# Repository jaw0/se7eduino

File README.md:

small atmel SAM S70 (300MHz cortex-M7) based dev board.
similar to the arduino due, except super-mega-turbocharged.

* 300 MHz ARM cortex-M7
* 2MB flash
* 384k RAM
* 480 Mbps high-speed USB
* micro sd card
* battery charger
* 64 x 34 mm

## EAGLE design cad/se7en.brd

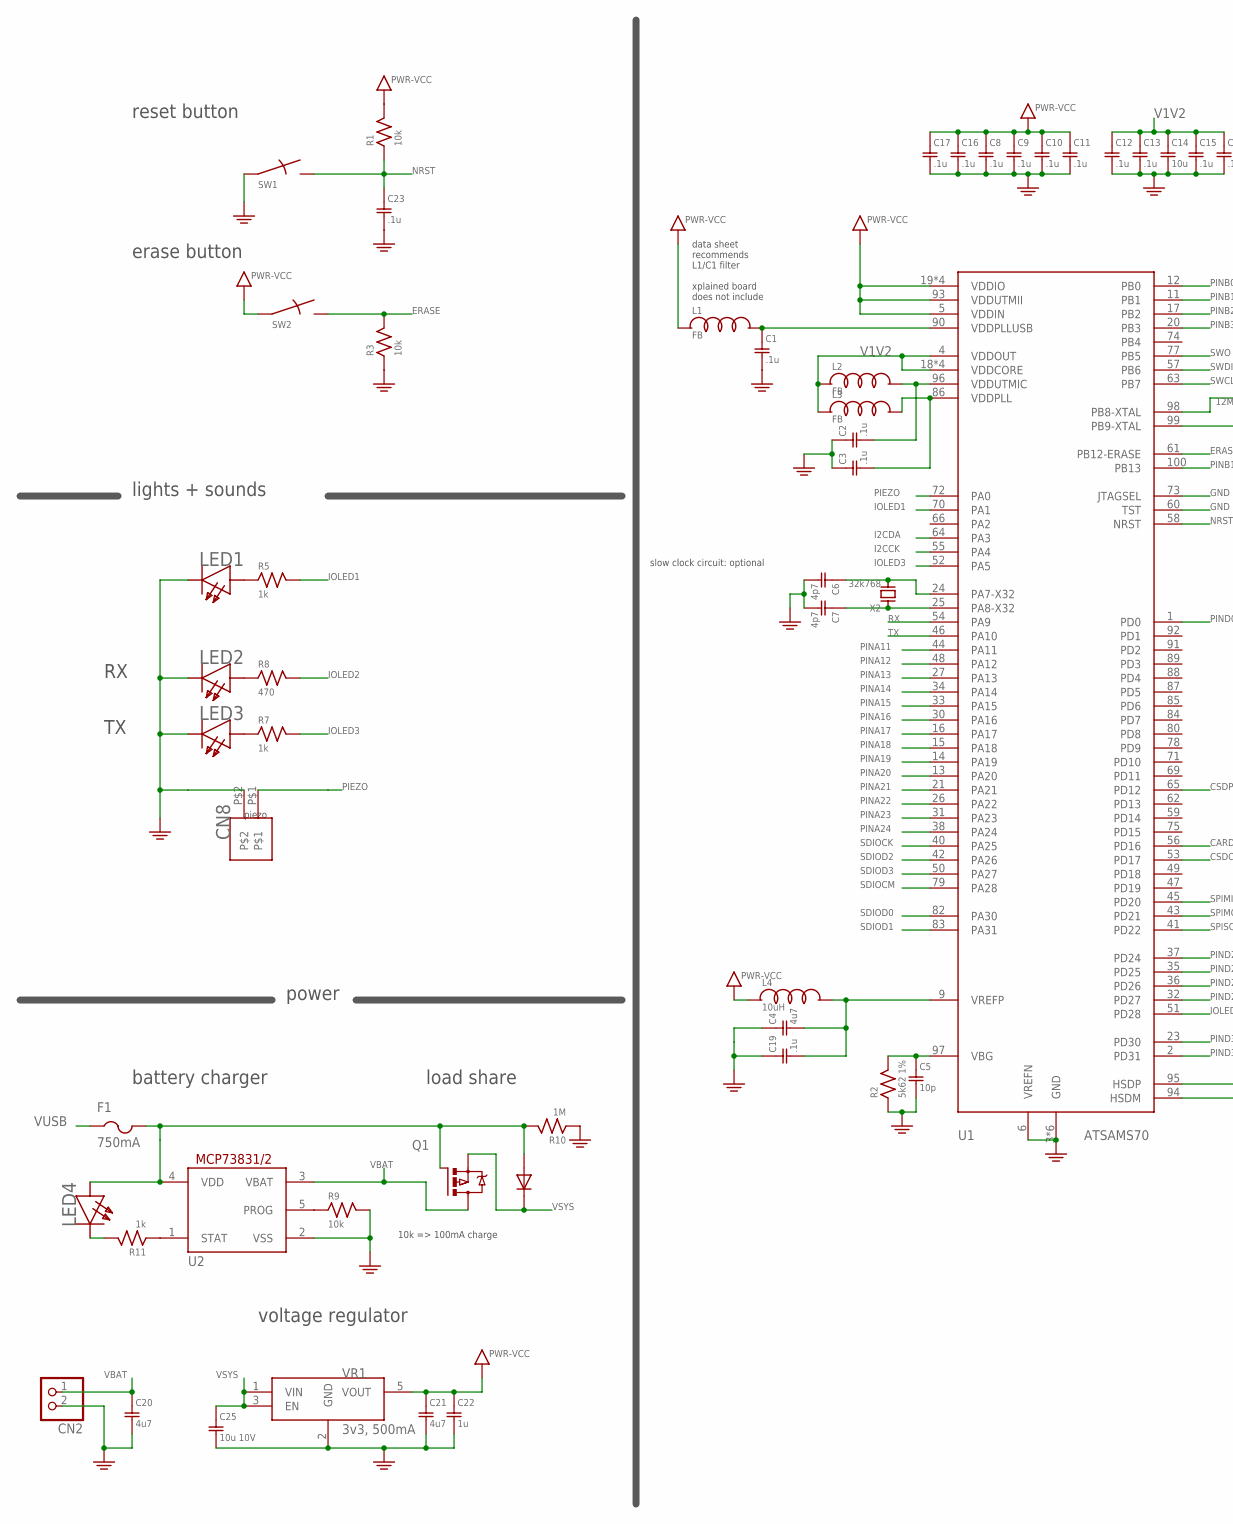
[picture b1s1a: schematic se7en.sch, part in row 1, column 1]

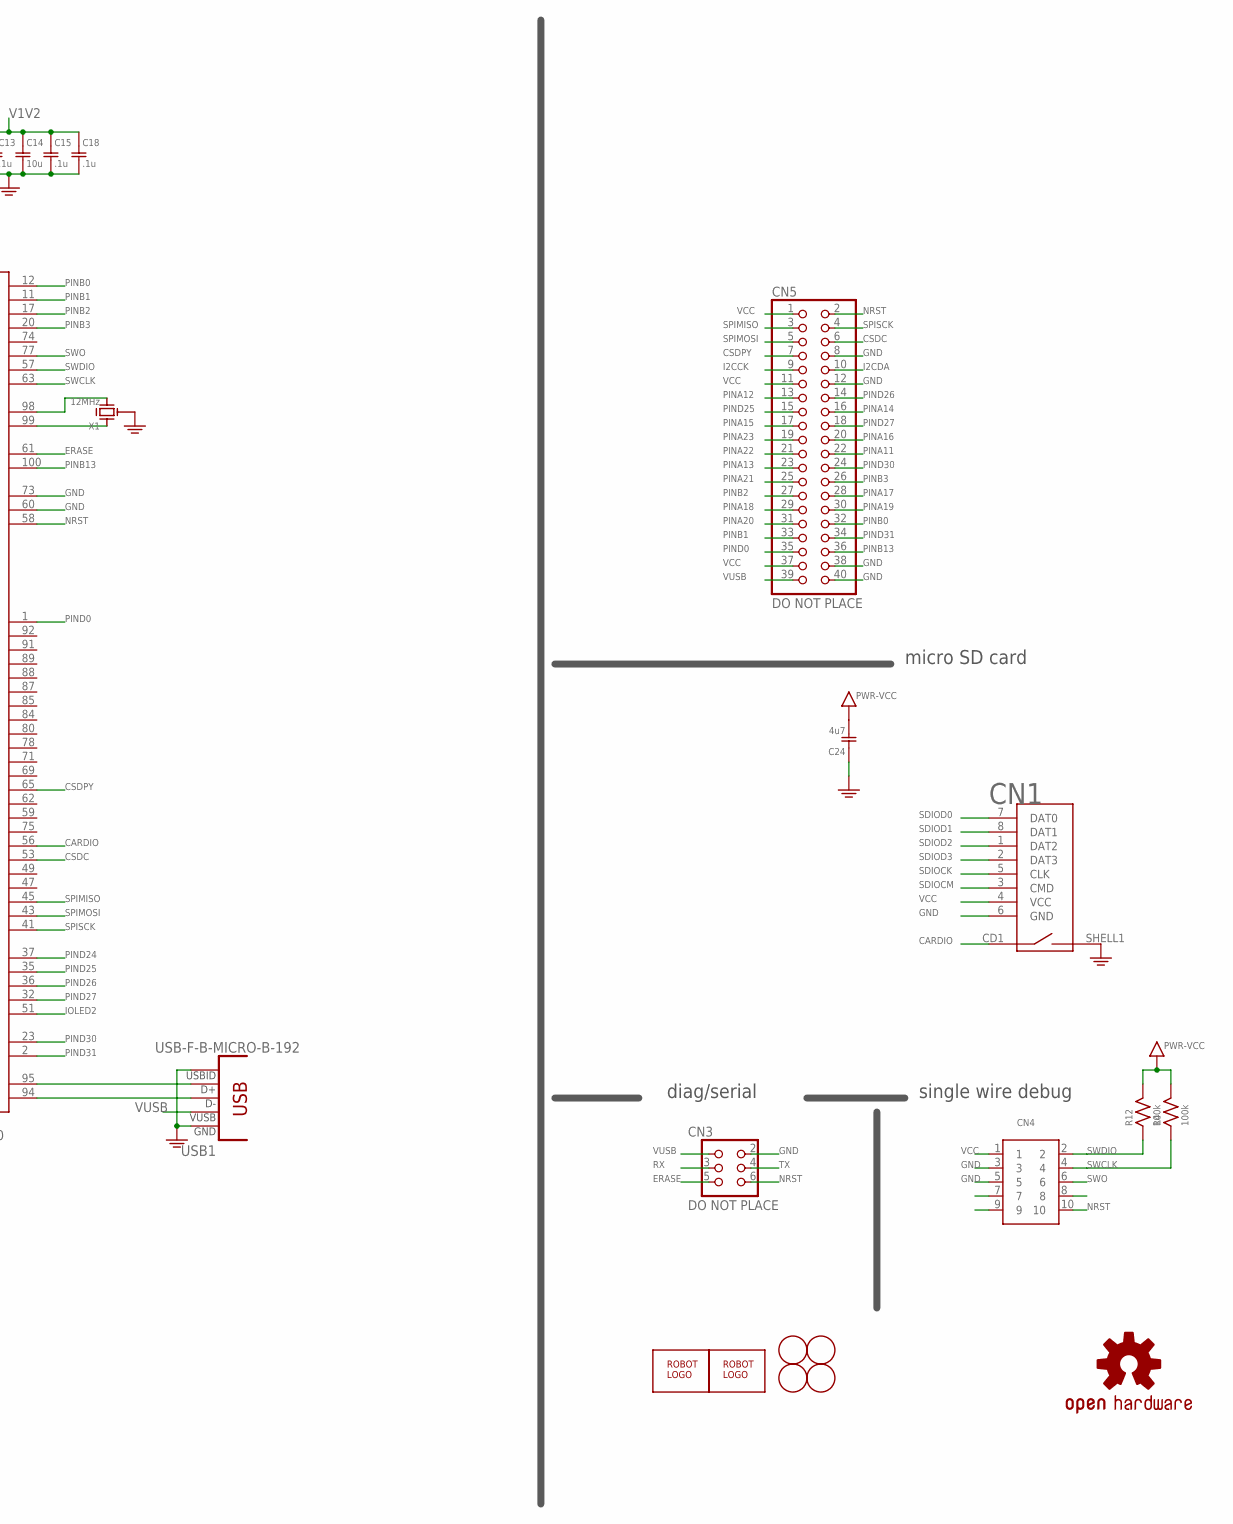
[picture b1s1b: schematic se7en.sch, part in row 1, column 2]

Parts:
C1, C2, C3, C8, C9, C10, C11, C12, C13, C15, C16, C17, C18, C19, C23: .1u; SMD0402
C4, C20, C21, C24: 4u7; SMD0603
C5: 10p; SMD0402
C6, C7: 4p7; SMD0402
C14: 10u; SMD0603
C22: 1u; SMD0603
C25: 10u 10V; SMD0603
CN1: MICROSD-EJECT; MICROSD/EJECTOR
CN2: JST_2PIN-SMT-RA; JST-PH-2-SMT-RA
CN3: DO NOT PLACE; HEADER-3X2-POGO
CN4: DO NOT PLACE; M127-5X2-F
CN5: DO NOT PLACE; 2X20
CN8: DO NOT PLACE; HEADER-1X2-THM-TIGHT
F1: 750mA; SMD1206
L1, L2, L3: FB; SMD0402
L4: 10uH; SMD0603
LED1: white; SMD0603D
LED2: green; SMD0603D
LED3: orange; SMD0603D
LED4: RED; SMD0603D
LOGO$1: OSHW-LOGOM; OSHW-LOGO-M
Q1: FDC6392S; SOT-23-6
R1, R3, R9: 10k; SMD0402
R2: 5k62 1%; SMD0402
R4, R12: 100k; SMD0402
R5, R7, R11: 1k; SMD0402
R8: 470; SMD0402
R10: 1M; SMD0402
SW1, SW2: SWITCHKMR211; KMR211
U1: ATSAMS70; TQFP-100-14X14MM
U2: MCP73831; SOT-23-5
U$1, U$3: ROBOTMAN-LOGO2
U$2, U$4, U$5, U$6: FIDUCIAL; FIDUCIAL_1MM
USB1: USB-F-B-MICRO-B-192; USB-MICRO-B-192
VR1: 3v3, 500mA; SOT-23-5
X1: 12MHz; RESONATOR-CSTCE
X2: 32k768; XTAL-32X15

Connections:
CARDIO: CN1.CD1 (SW1), U1.56 (PD16)
CSDC: CN5.6, U1.53 (PD17)
CSDPY: CN5.7, U1.65 (PD12)
ERASE: CN3.5, R3.2, SW2.2, SW2.4, U1.61 (PB12-ERASE)
GND: C1.2, C2.1, C3.1, C4.1, C5.2, C6.2, C7.2, C8.2, C9.2, C10.2, C11.2, C12.2, C13.2, C14.2, C15.2, C16.2, C17.2, C18.2, C19.1, C20.2, C21.2, C22.2, C23.2, C24.1, C25.2, CN1.6 (GND), CN1.SHELL1 (SW2), CN2.2 (1), CN3.2, CN4.3, CN4.5, CN5.8, CN5.12, CN5.38, CN5.40, CN8.P$2, LED1.C, LED2.C, LED3.C, R2.1, R3.1, R9.2, R10.1, SW1.1, SW1.3, U1.3 (GND), U1.6 (VREFN), U1.7 (GND), U1.8 (GND), U1.10 (GND), U1.29 (GND), U1.60 (TST), U1.67 (GND), U1.73 (JTAGSEL), U2.2 (VSS), USB1.P4 (USBID), USB1.P5 (GND), VR1.2 (GND), X1.2 (G)
I2CCK: CN5.9, U1.55 (PA4)
I2CDA: CN5.10, U1.64 (PA3)
IOLED1: R5.2, U1.70 (PA1)
IOLED2: R8.2, U1.51 (PD28)
IOLED3: R7.2, U1.52 (PA5)
unnamed: C2.2, L2.2, U1.96 (VDDUTMIC)
unnamed: C1.1, L1.2, U1.90 (VDDPLLUSB)
unnamed: C3.2, L3.2, U1.86 (VDDPLL)
unnamed: LED2.A, R8.1
unnamed: LED3.A, R7.1
unnamed: U1.98 (PB8-XTAL), X1.3 (X2)
unnamed: C5.1, R2.2, U1.97 (VBG)
unnamed: U1.99 (PB9-XTAL), X1.1 (X1)
unnamed: C7.1, U1.25 (PA8-X32), X2.P$1
unnamed: R11.1, U2.1 (STAT)
unnamed: C6.1, U1.24 (PA7-X32), X2.P$2
unnamed: LED4.C, R11.2
unnamed: LED1.A, R5.1
unnamed: R9.1, U2.5 (PROG)
NRST: C23.1, CN3.6, CN4.10, CN5.2, R1.1, SW1.2, SW1.4, U1.58 (NRST)
PIEZO: CN8.P$1, U1.72 (PA0)
PINA11: CN5.22, U1.44 (PA11)
PINA12: CN5.13, U1.48 (PA12)
PINA13: CN5.23, U1.27 (PA13)
PINA14: CN5.16, U1.34 (PA14)
PINA15: CN5.17, U1.33 (PA15)
PINA16: CN5.20, U1.30 (PA16)
PINA17: CN5.28, U1.16 (PA17)
PINA18: CN5.29, U1.15 (PA18)
PINA19: CN5.30, U1.14 (PA19)
PINA20: CN5.31, U1.13 (PA20)
PINA21: CN5.25, U1.21 (PA21)
PINA22: CN5.21, U1.26 (PA22)
PINA23: CN5.19, U1.31 (PA23)
PINA24: U1.38 (PA24)
PINB0: CN5.32, U1.12 (PB0)
PINB1: CN5.33, U1.11 (PB1)
PINB2: CN5.27, U1.17 (PB2)
PINB3: CN5.26, U1.20 (PB3)
PINB13: CN5.36, U1.100 (PB13)
PIND0: CN5.35, U1.1 (PD0)
PIND24: U1.37 (PD24)
PIND25: CN5.15, U1.35 (PD25)
PIND26: CN5.14, U1.36 (PD26)
PIND27: CN5.18, U1.32 (PD27)
PIND30: CN5.24, U1.23 (PD30)
PIND31: CN5.34, U1.2 (PD31)
RX: CN3.3, U1.54 (PA9)
SDIOCK: CN1.5 (CLK), U1.40 (PA25)
SDIOCM: CN1.3 (CMD), U1.79 (PA28)
SDIOD0: CN1.7 (DAT0), U1.82 (PA30)
SDIOD1: CN1.8 (DAT1), U1.83 (PA31)
SDIOD2: CN1.1 (DAT2), U1.42 (PA26)
SDIOD3: CN1.2 (DAT3), U1.50 (PA27)
SPIMISO: CN5.3, U1.45 (PD20)
SPIMOSI: CN5.5, U1.43 (PD21)
SPISCK: CN5.4, U1.41 (PD22)
SWCLK: CN4.4, R4.1, U1.63 (PB7)
SWDIO: CN4.2, R12.1, U1.57 (PB6)
SWO: CN4.6, U1.77 (PB5)
TX: CN3.4, U1.46 (PA10)
USBDM: U1.94 (HSDM), USB1.P2 (D-)
USBDP: U1.95 (HSDP), USB1.P3 (D+)
V1V2: C12.1, C13.1, C14.1, C15.1, C18.1, L2.1, L3.1, U1.4 (VDDOUT), U1.18 (VDDCORE), U1.22 (VDDCORE), U1.39 (VDDCORE), U1.76 (VDDCORE)
VBAT: C20.1, CN2.1 (2), Q1.4 (D), U2.3 (VBAT)
VCC: C8.1, C9.1, C10.1, C11.1, C16.1, C17.1, C21.1, C22.1, C24.2, CN1.4 (VCC), CN4.1, CN5.1, CN5.11, CN5.37, L1.1, L4.1, R1.2, R4.2, R12.2, SW2.1, SW2.3, U1.5 (VDDIN), U1.19 (VDDIO), U1.28 (VDDIO), U1.68 (VDDIO), U1.81 (VDDIO), U1.93 (VDDUTMII), VR1.5 (VOUT)
VCCA: C4.2, C19.2, L4.2, U1.9 (VREFP)
VIN: F1.2, LED4.A, Q1.1 (A), Q1.3 (G), R10.2, U2.4 (VDD)
VSYS: C25.1, Q1.2 (S), Q1.6 (C), VR1.1 (VIN), VR1.3 (EN)
VUSB: CN3.1, CN5.39, F1.1, USB1.P1 (VUSB)

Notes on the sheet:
piezo
battery charger
load share
voltage regulator
diag/serial
single wire debug
micro SD card
reset button
erase button
lights + sounds
power
slow clock circuit: optional
data sheet recommends L1/C1 filter xplained board does not include
10k => 100mA charge

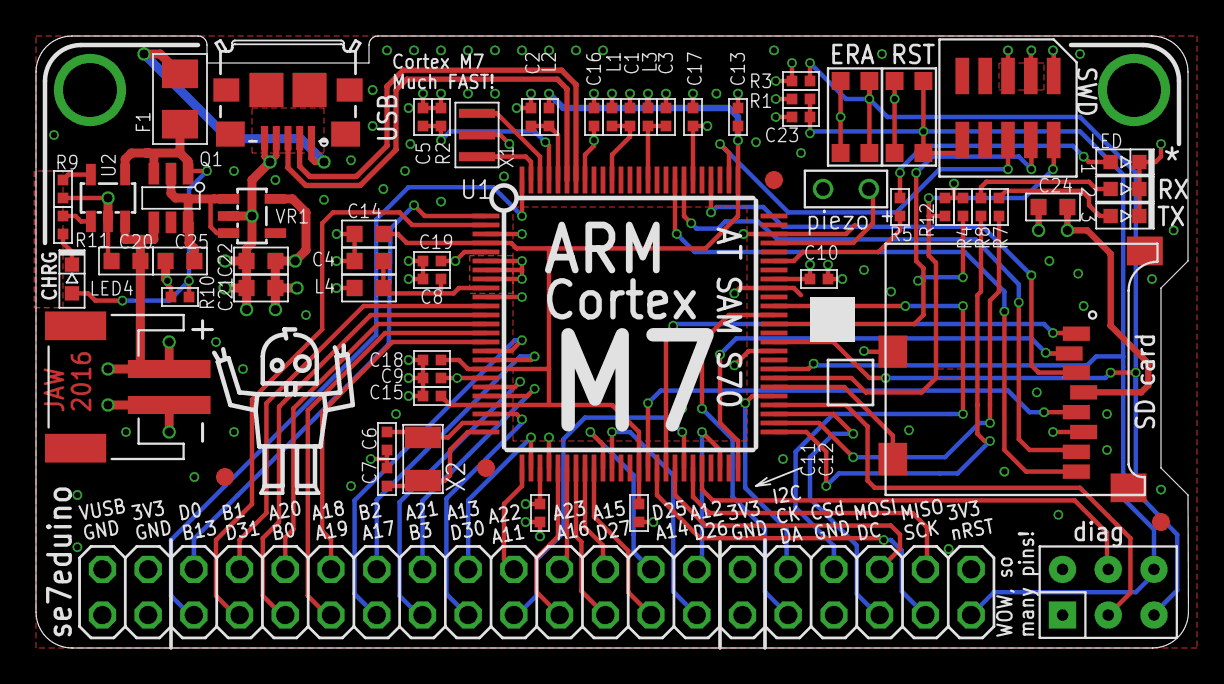
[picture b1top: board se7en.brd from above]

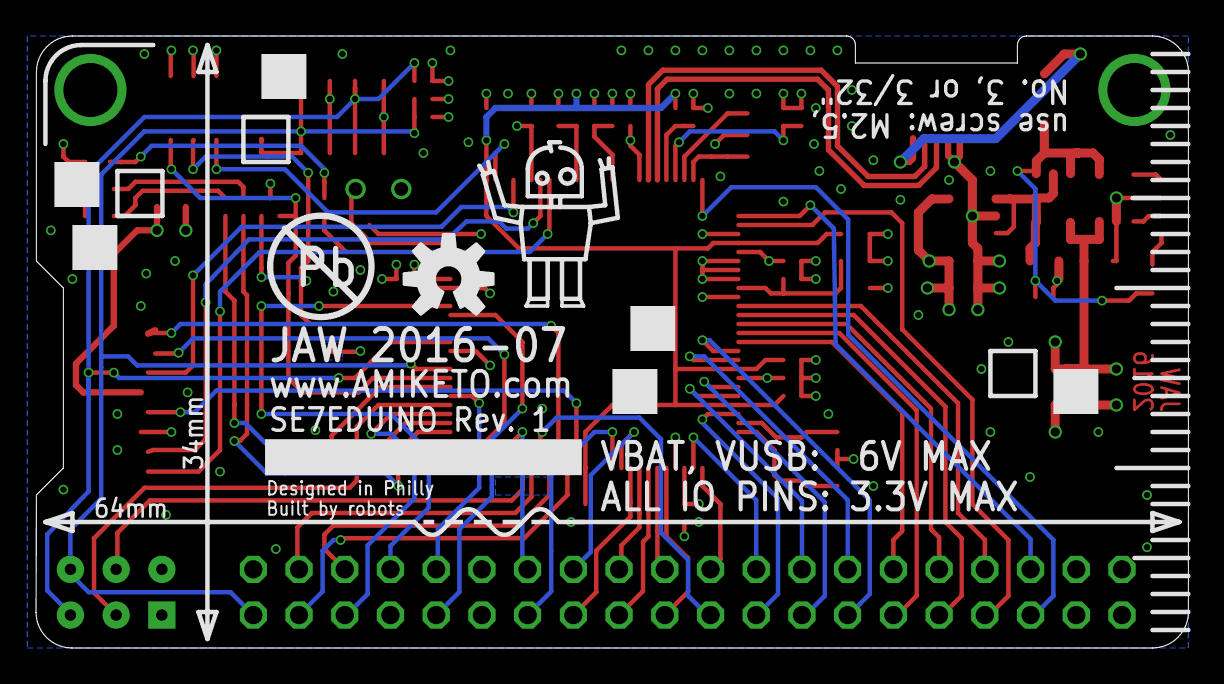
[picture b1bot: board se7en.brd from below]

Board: 4 copper layers, 64.0 x 34.0 mm, 67 parts (2 on the bottom side), 73 nets.

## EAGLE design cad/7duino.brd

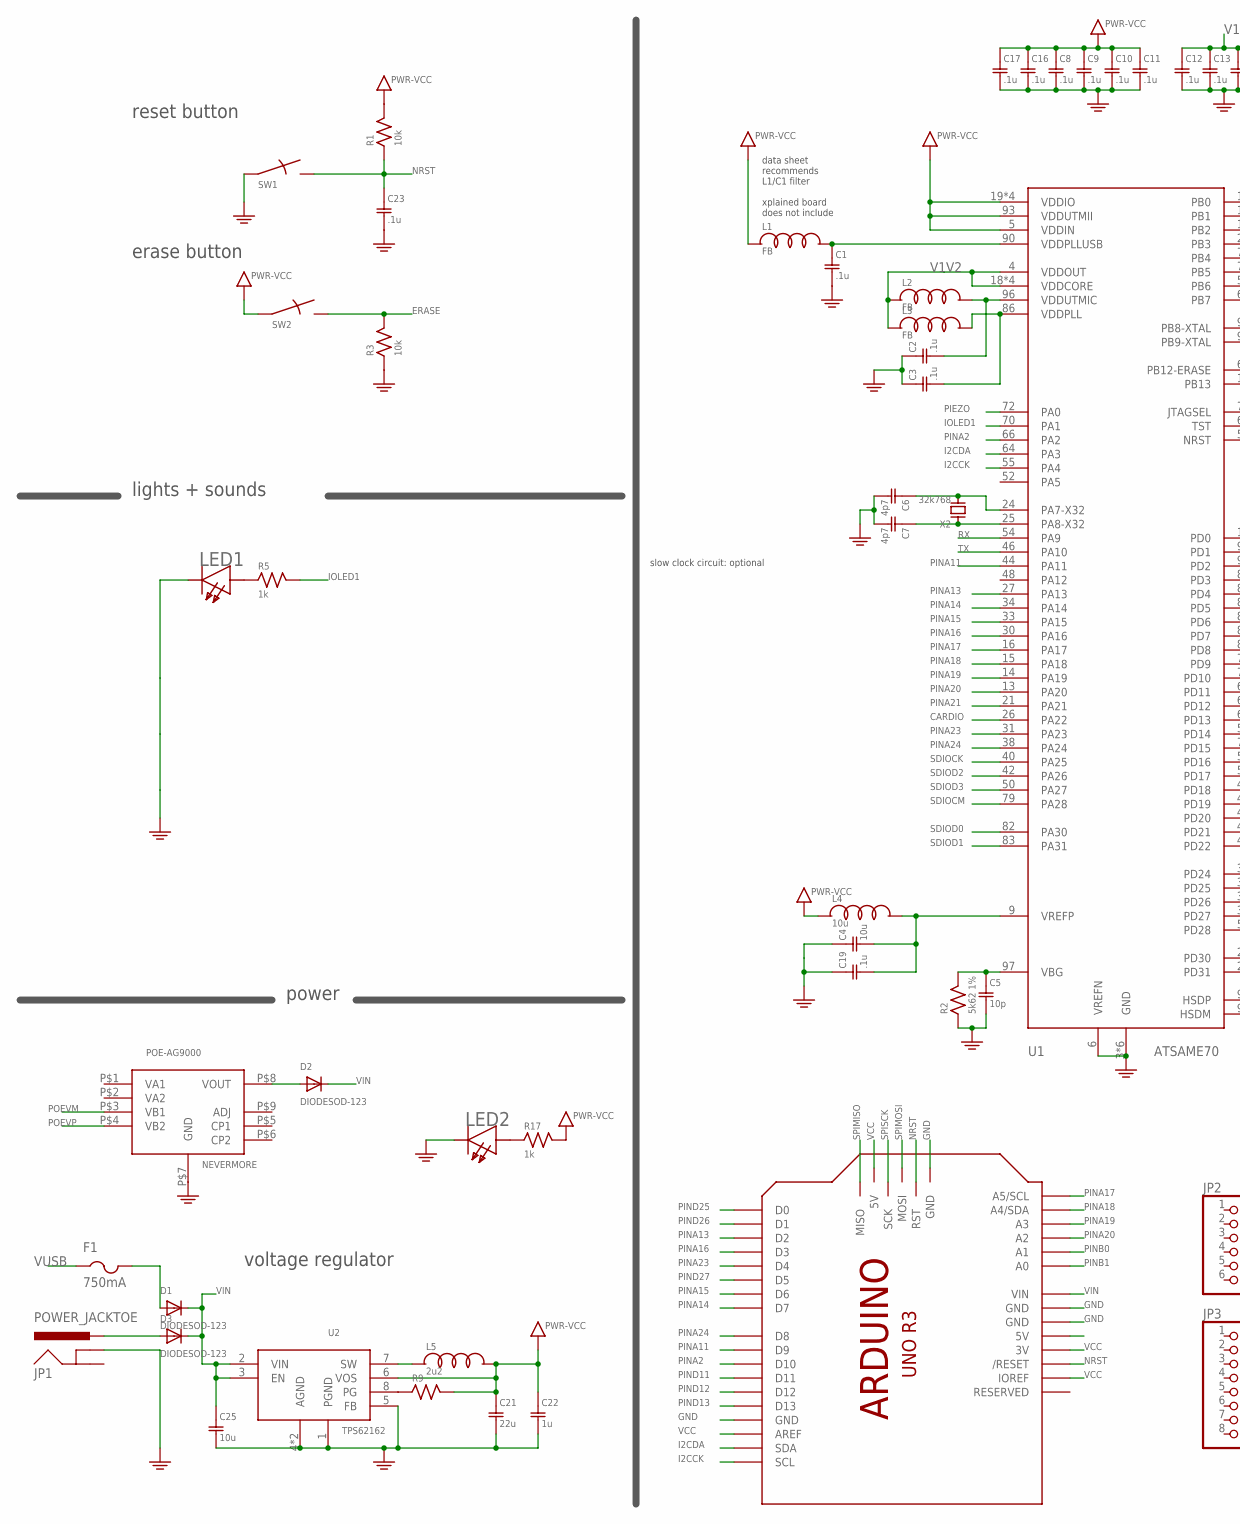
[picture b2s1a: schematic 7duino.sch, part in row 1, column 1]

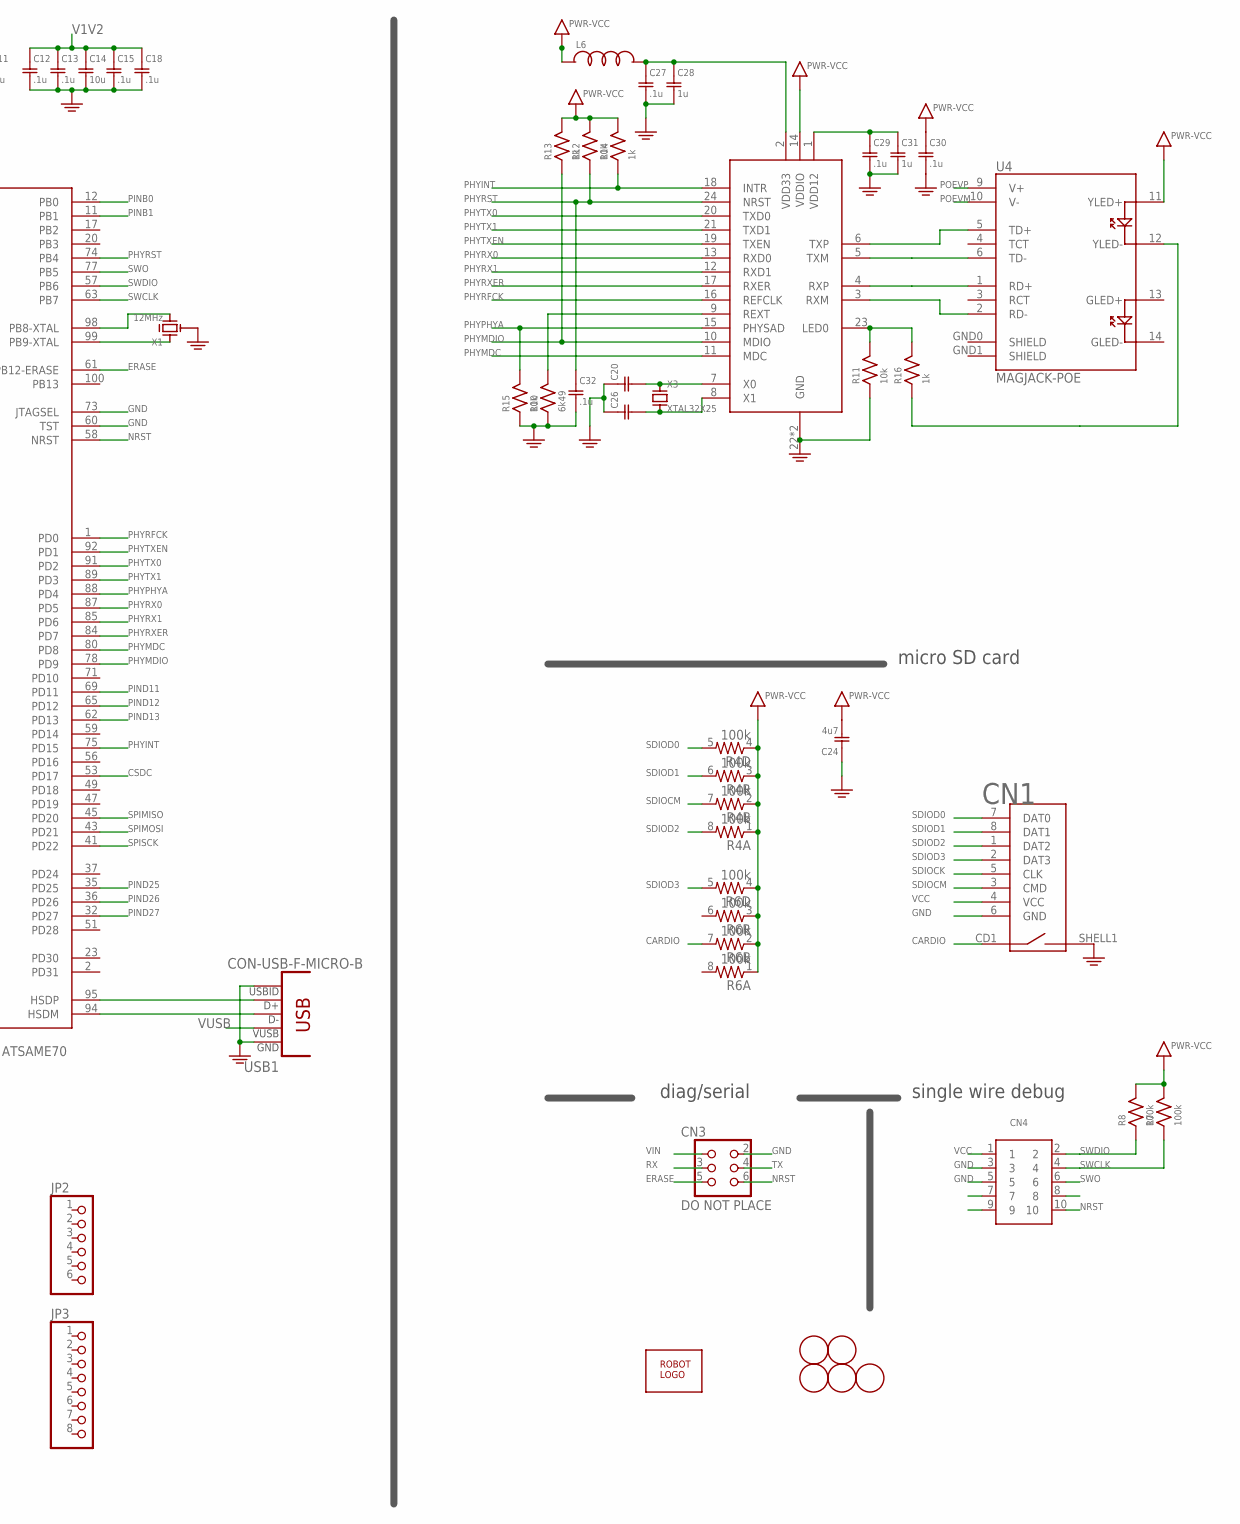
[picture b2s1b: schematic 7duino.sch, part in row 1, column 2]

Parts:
C1, C2, C3, C8, C9, C10, C11, C12, C13, C15, C16, C17, C18, C19, C23, C27, C29, C30, C32: .1u; SMD0402
C4, C14, C25: 10u; SMD0603
C5: 10p; SMD0402
C6, C7: 4p7; SMD0402
C20, C26: C-0402; SMD0402
C21: 22u; SMD0805
C22, C28, C31: 1u; SMD0402
C24: 4u7; SMD0603
CN1: MICROSD-EJECT; MICROSD/EJECTOR
CN3: DO NOT PLACE; HEADER-3X2-POGO
CN4: DO NOT PLACE; M127-5X2-F
D1, D2, D3: DIODESOD-123; SOD-123
F1: 750mA; SMD1206
JP1: POWER_JACKTOE; POWER_JACK_SMD_OVERPASTE_TOE
JP2: PINHD-1X6CLEAN; 1X06-CLEAN
JP3: PINHD-1X8CLEANBIG; 1X08-CLEANBIG
L1, L2, L3: FB; SMD0402
L4: 10u; SMD0402
L5: 2u2; SMD1210
L6: L-0402; SMD0402
LED1, LED2: white; SMD0603D
M1: ARDUINO_R3_ICSP_NODIM; ARDUINOR3_ICSP_NODIM
NEVERMORE: POE-AG9000
R1, R3, R11, R12, R15: 10k; SMD0402
R2: 5k62 1%; SMD0402
R4, R6: 100k; SMD-0603-ARV
R5, R13, R14, R16, R17: 1k; SMD0402
R7, R8: 100k; SMD0402
R9: R-0402; SMD0402
R10: 6k49; SMD0402
SW1, SW2: SWITCHKMR211; KMR211
U1: ATSAME70; TQFP-100-14X14MM
U2: TPS62162; WSON8
U3: KSZ8081RNA; LGA24EP
U4: MAGJACK-POE
U$1: ROBOTMAN-LOGO2
U$2, U$3, U$4, U$5, U$6: FIDUCIAL; FIDUCIAL_1MM
USB1: CON-USB-F-MICRO-B; CONN_USB_MICRO-B
X1: 12MHz; RESONATOR-CSTCE
X2: 32k768; XTAL-32X15
X3: XTAL32X25; XTAL-32X25

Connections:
CARDIO: CN1.CD1 (SW1), R6.7 (2), U1.26 (PA22)
CSDC: U1.53 (PD17)
ERASE: CN3.5, R3.2, SW2.2, SW2.4, U1.61 (PB12-ERASE)
GND: C1.2, C2.1, C3.1, C4.1, C5.2, C6.2, C7.2, C8.2, C9.2, C10.2, C11.2, C12.2, C13.2, C14.2, C15.2, C16.2, C17.2, C18.2, C19.1, C20.1, C21.2, C22.2, C23.2, C24.1, C25.2, C26.1, C27.2, C28.2, C29.2, C30.2, C31.2, C32.2, CN1.6 (GND), CN1.SHELL1 (SW2), CN3.2, CN4.3, CN4.5, JP1.GND (GNDBREAK), LED1.C, LED2.C, M1.GND, M1.GND@1 (GND), M1.GND@2 (GND), M1.GND@3 (GND), NEVERMORE.P$7 (GND), R2.1, R3.1, R10.1, R11.1, R15.1, SW1.1, SW1.3, U1.3 (GND), U1.6 (VREFN), U1.7 (GND), U1.8 (GND), U1.10 (GND), U1.29 (GND), U1.60 (TST), U1.67 (GND), U1.73 (JTAGSEL), U2.1 (PGND), U2.4 (AGND), U2.5 (FB), U2.P$9 (AGND), U3.22 (GND), U3.P$1 (GND), USB1.P4 (USBID), USB1.P5 (GND), X1.2 (G)
I2CCK: M1.SCL, U1.55 (PA4)
I2CDA: M1.SDA, U1.64 (PA3)
IOLED1: R5.2, U1.70 (PA1)
unnamed: C2.2, L2.2, U1.96 (VDDUTMIC)
unnamed: C1.1, L1.2, U1.90 (VDDPLLUSB)
unnamed: C3.2, L3.2, U1.86 (VDDPLL)
unnamed: LED2.A, R17.1
unnamed: D2.A, NEVERMORE.P$8 (VOUT)
unnamed: U1.98 (PB8-XTAL), X1.3 (X2)
unnamed: C5.1, R2.2, U1.97 (VBG)
unnamed: U1.99 (PB9-XTAL), X1.1 (X1)
unnamed: C7.1, U1.25 (PA8-X32), X2.P$1
unnamed: L5.1, U2.7 (SW)
unnamed: C6.1, U1.24 (PA7-X32), X2.P$2
unnamed: U3.6 (TXP), U4.5 (TD+)
unnamed: D3.A, JP1.VIN0 (PWR)
unnamed: LED1.A, R5.1
unnamed: U3.5 (TXM), U4.6 (TD-)
unnamed: R9.1, U2.8 (PG)
unnamed: U3.4 (RXP), U4.1 (RD+)
unnamed: U3.3 (RXM), U4.2 (RD-)
unnamed: C20.2, U3.7 (X0), X3.1
unnamed: C26.2, U3.8 (X1), X3.3
unnamed: C29.1, C31.1, U3.1 (VDD12)
unnamed: C27.1, C28.1, L6.2, U3.2 (VDD33)
unnamed: R10.2, U3.9 (REXT)
unnamed: R11.2, R16.2, U3.23 (LED0)
unnamed: D1.A, F1.2
unnamed: R16.1, U4.12 (YLED-)
NRST: C23.1, CN3.6, CN4.10, M1.RESET (/RESET), M1.RESET_ICSP (RST), R1.1, SW1.2, SW1.4, U1.58 (NRST)
PHYINT: R14.1, U1.75 (PD15), U3.18 (INTR)
PHYMDC: U1.80 (PD8), U3.11 (MDC)
PHYMDIO: R13.1, U1.78 (PD9), U3.10 (MDIO)
PHYPHYA: R15.2, U1.88 (PD4), U3.15 (PHYSAD)
PHYRFCK: U1.1 (PD0), U3.16 (REFCLK)
PHYRST: C32.1, R12.1, U1.74 (PB4), U3.24 (NRST)
PHYRX0: U1.87 (PD5), U3.13 (RXD0)
PHYRX1: U1.85 (PD6), U3.12 (RXD1)
PHYRXER: U1.84 (PD7), U3.17 (RXER)
PHYTX0: U1.91 (PD2), U3.20 (TXD0)
PHYTX1: U1.89 (PD3), U3.21 (TXD1)
PHYTXEN: U1.92 (PD1), U3.19 (TXEN)
PIEZO: U1.72 (PA0)
PINA2: M1.D10, U1.66 (PA2)
PINA11: M1.D9, U1.44 (PA11)
PINA13: M1.D2, U1.27 (PA13)
PINA14: M1.D7, U1.34 (PA14)
PINA15: M1.D6, U1.33 (PA15)
PINA16: M1.D3, U1.30 (PA16)
PINA17: M1.A5 (A5/SCL), U1.16 (PA17)
PINA18: M1.A4 (A4/SDA), U1.15 (PA18)
PINA19: M1.A3, U1.14 (PA19)
PINA20: M1.A2, U1.13 (PA20)
PINA21: U1.21 (PA21)
PINA23: M1.D4, U1.31 (PA23)
PINA24: M1.D8, U1.38 (PA24)
PINB0: M1.A1, U1.12 (PB0)
PINB1: M1.A0, U1.11 (PB1)
PIND11: M1.D11, U1.69 (PD11)
PIND12: M1.D12, U1.65 (PD12)
PIND13: M1.D13, U1.62 (PD13)
PIND25: M1.D0, U1.35 (PD25)
PIND26: M1.D1, U1.36 (PD26)
PIND27: M1.D5, U1.32 (PD27)
POEVM: NEVERMORE.P$3 (VB1), U4.10 (V-)
POEVP: NEVERMORE.P$4 (VB2), U4.9 (V+)
RX: CN3.3, U1.54 (PA9)
SDIOCK: CN1.5 (CLK), U1.40 (PA25)
SDIOCM: CN1.3 (CMD), R4.7 (2), U1.79 (PA28)
SDIOD0: CN1.7 (DAT0), R4.5 (2), U1.82 (PA30)
SDIOD1: CN1.8 (DAT1), R4.6 (2), U1.83 (PA31)
SDIOD2: CN1.1 (DAT2), R4.8 (2), U1.42 (PA26)
SDIOD3: CN1.2 (DAT3), R6.5 (2), U1.50 (PA27)
SPIMISO: M1.MISO, U1.45 (PD20)
SPIMOSI: M1.MOSI, U1.43 (PD21)
SPISCK: M1.SCK, U1.41 (PD22)
SWCLK: CN4.4, R7.1, U1.63 (PB7)
SWDIO: CN4.2, R8.1, U1.57 (PB6)
SWO: CN4.6, U1.77 (PB5)
TX: CN3.4, U1.46 (PA10)
USBDM: U1.94 (HSDM), USB1.P2 (D-)
USBDP: U1.95 (HSDP), USB1.P3 (D+)
V1V2: C12.1, C13.1, C14.1, C15.1, C18.1, L2.1, L3.1, U1.4 (VDDOUT), U1.18 (VDDCORE), U1.22 (VDDCORE), U1.39 (VDDCORE), U1.76 (VDDCORE)
VCC: C8.1, C9.1, C10.1, C11.1, C16.1, C17.1, C21.1, C22.1, C24.2, C30.1, CN1.4 (VCC), CN4.1, L1.1, L4.1, L5.2, L6.1, M1.3V, M1.5V_ICSP (5V), M1.AREF, M1.IOREF, R1.2, R4.1, R4.2 (1), R4.3 (1), R4.4 (1), R6.1, R6.2 (1), R6.3 (1), R6.4 (1), R7.2, R8.2, R9.2, R12.2, R13.2, R14.2, R17.2, SW2.1, SW2.3, U1.5 (VDDIN), U1.19 (VDDIO), U1.28 (VDDIO), U1.68 (VDDIO), U1.81 (VDDIO), U1.93 (VDDUTMII), U2.6 (VOS), U3.14 (VDDIO), U4.11 (YLED+)
VCCA: C4.2, C19.2, L4.2, U1.9 (VREFP)
VIN: C25.1, CN3.1, D1.C, D2.C, D3.C, M1.VIN, U2.2 (VIN), U2.3 (EN)
VUSB: F1.1, USB1.P1 (VUSB)

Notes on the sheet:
voltage regulator
diag/serial
single wire debug
micro SD card
reset button
erase button
lights + sounds
power
slow clock circuit: optional
data sheet recommends L1/C1 filter xplained board does not include

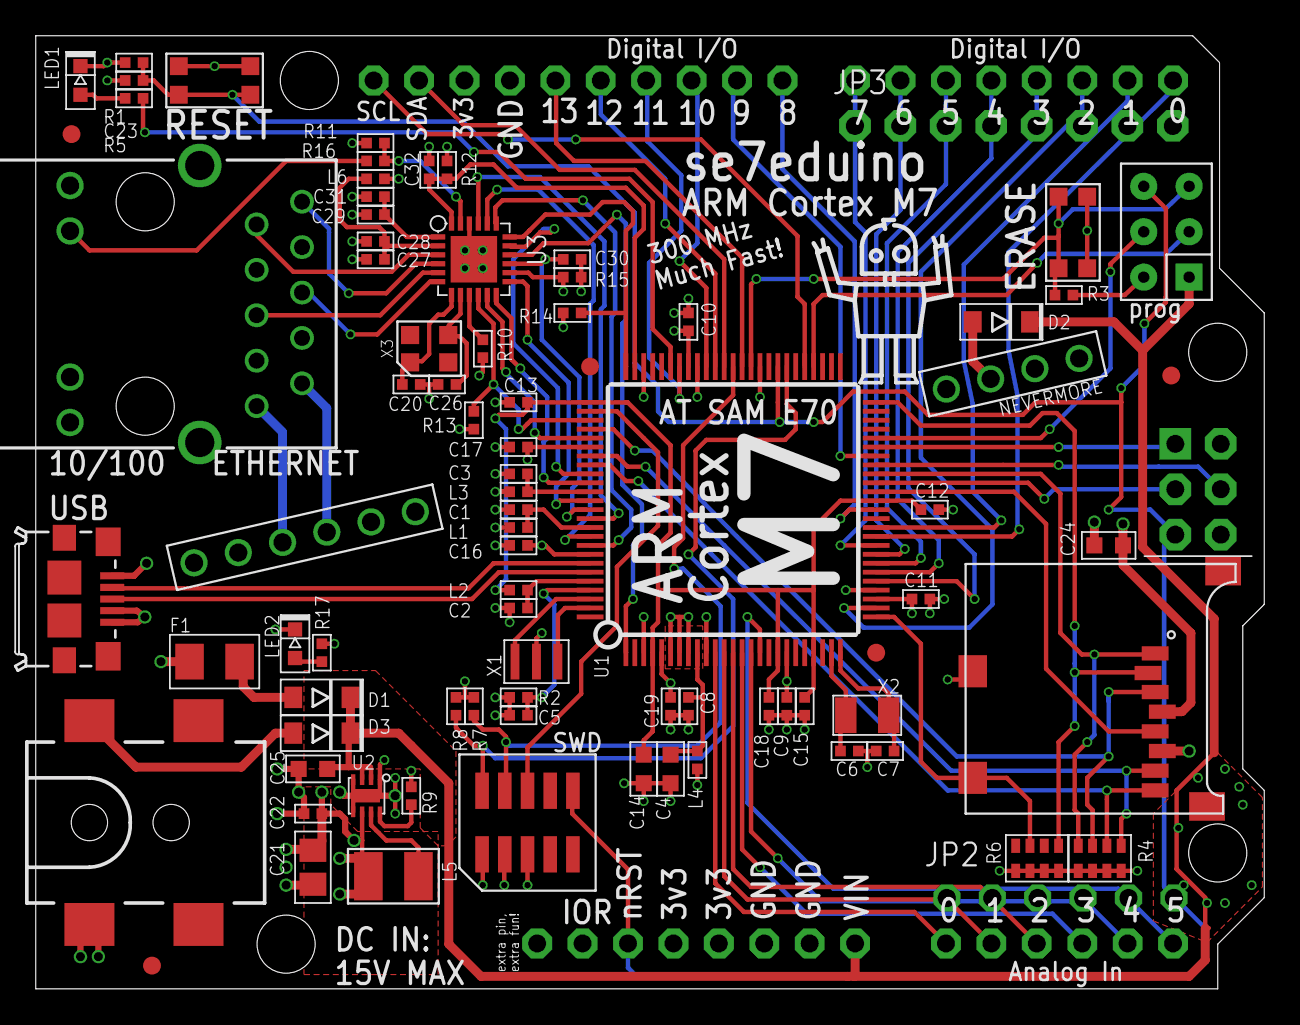
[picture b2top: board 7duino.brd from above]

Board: 4 copper layers, 68.7 x 53.3 mm, 85 parts (0 on the bottom side), 88 nets.

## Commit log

2016-05-28 atmel sam s70 board
2016-05-28 remove unused part
2016-05-29 charger
2016-05-29 tweak
2016-05-29 replace A22 with A12
2016-05-30 smaller/cheaper regulator
2016-06-08 new board
2016-06-09 move files
2016-06-19 add files
2016-06-19 itemize passives
2016-06-21 fix typo
2016-06-21 tweak orientation
2016-06-26 scootch back from edge, tweak silk
2016-06-29 remove pullups (use pio pullups)
2016-07-01 move LEDs
2016-07-03 piezo conn
2016-07-06 usb improve Zd
2016-07-07 drop vbat pins, add more io
2016-08-02 brighten green
2016-08-21 update pdf

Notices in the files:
parts and their libraries:
SparkFun-Connectors: Licensing: Creative Commons ShareAlike 4.0 International - https://creativecommons.org/licenses/by-sa/4.0
